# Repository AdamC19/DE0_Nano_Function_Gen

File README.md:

# DE0-Nano Function Gen
This repo contains the hardware files for a function generator built around the DE0-Nano FPGA dev board.

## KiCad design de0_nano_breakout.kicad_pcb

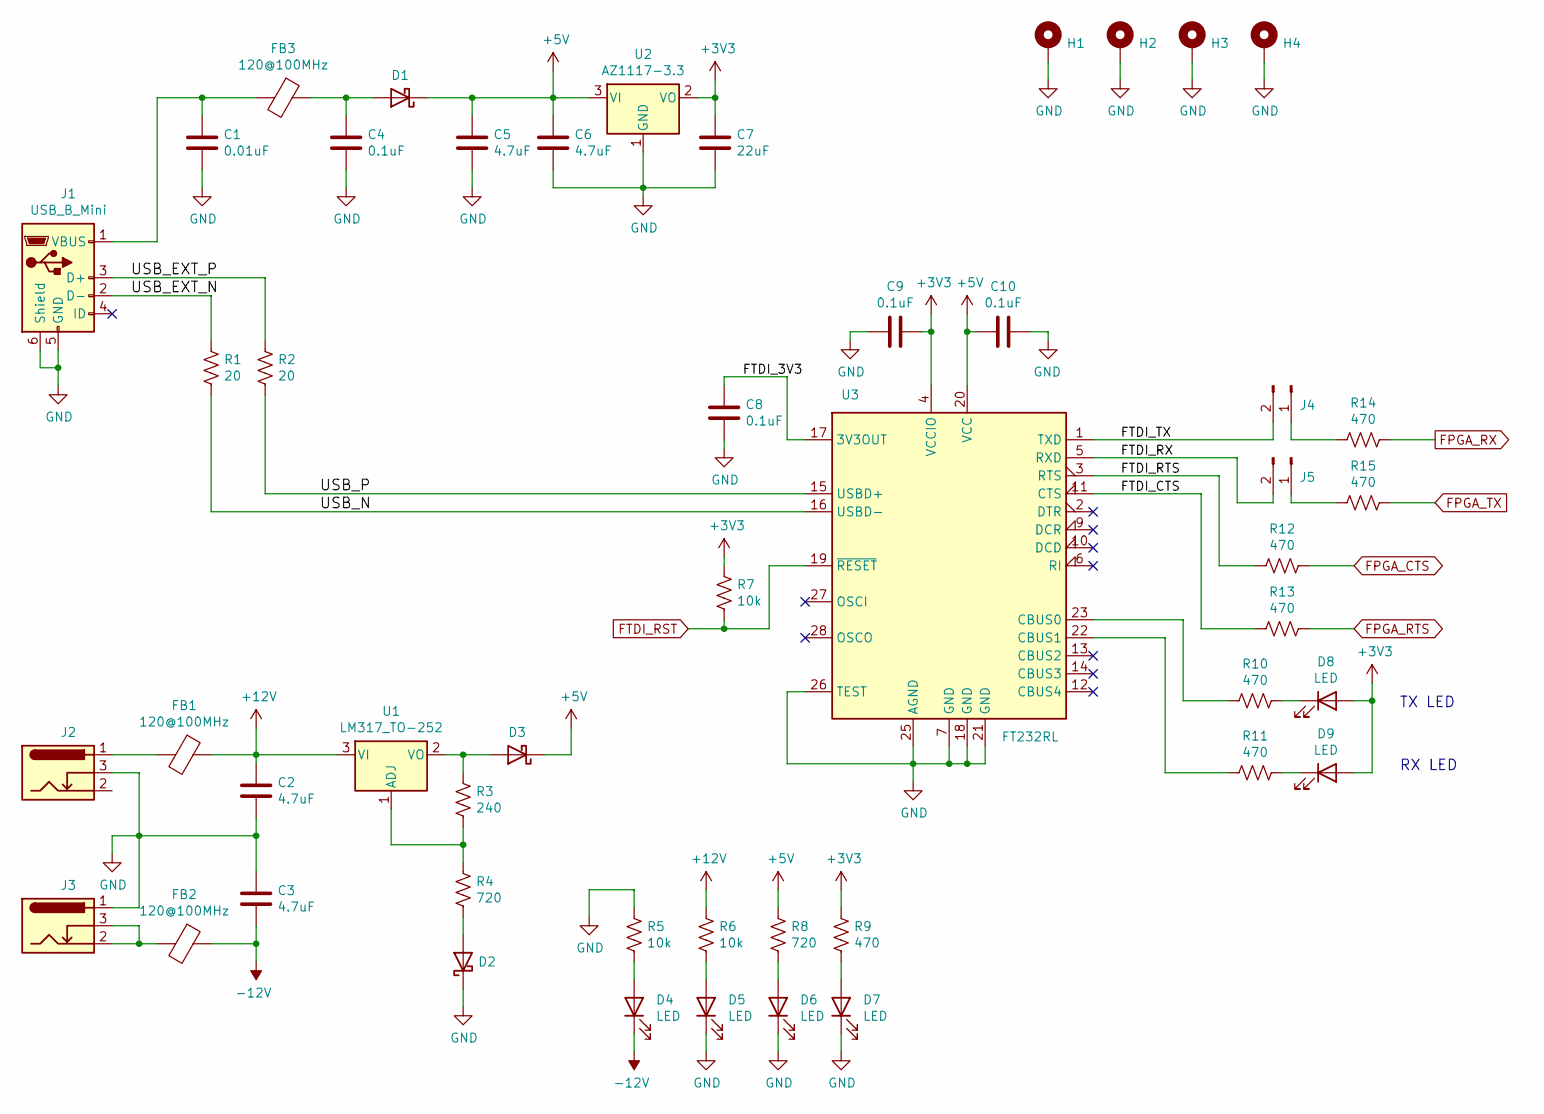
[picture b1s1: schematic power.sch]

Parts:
C1: 0.01uF; C_0603_1608Metric
C2, C3, C5, C6: 4.7uF; C_0805_2012Metric
C4, C8, C9, C10: 0.1uF; C_0603_1608Metric
C7: 22uF; C_1206_3216Metric
D1, D2, D3: D_Schottky; D_SMA
D4, D5, D6, D7, D8, D9: LED; LED_0603_1608Metric
FB1, FB2, FB3: 120@100MHz; L_0805_2012Metric
H1, H2, H3, H4: MountingHole_Pad; MountingHole_2.7mm_M2.5_Pad
J1: USB_B_Mini; USB_Mini-B_Wuerth_65100516121_Horizontal
J2, J3: Barrel_Jack_Switch; BarrelJack_Wuerth_6941xx301002
J4, J5: Conn_01x02_Male; PinHeader_1x02_P2.54mm_Vertical
R1, R2: 20; R_0805_2012Metric
R3: 240; R_0805_2012Metric
R4, R8: 720; R_0805_2012Metric
R5, R6, R7: 10k; R_0805_2012Metric
R9, R10, R11, R12, R13, R14, R15: 470; R_0805_2012Metric
U1: LM317_TO-252; TO-252-2
U2: AZ1117-3.3; SOT-89-3
U3: FT232RL; SSOP-28_5.3x10.2mm_P0.65mm

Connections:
+3V3: C7.1, C9.2, D8.2 (A), D9.2 (A), R7.1, R9.1, U2.2 (VO), U3.4 (VCCIO); also elsewhere on the board
+5V: C5.1, C6.1, C10.2, D1.1 (K), D3.1 (K), R8.1, U2.3 (VI), U3.20 (VCC); also elsewhere on the board
+12V: C2.1, FB1.1, R6.1, U1.3 (VI); also elsewhere on the board
-12V: C3.2, D4.1 (K), FB2.1; also elsewhere on the board
/Power/FTDI_3V3: C8.1, U3.17 (3V3OUT)
/Power/FTDI_CTS: R13.2, U3.11 (CTS)
/Power/FTDI_RTS: R12.2, U3.3 (RTS)
/Power/FTDI_RX: J5.2, U3.5 (RXD)
/Power/FTDI_TX: J4.2, U3.1 (TXD)
/Power/USB_EXT_N: J1.2 (D-), R1.2
/Power/USB_EXT_P: J1.3 (D+), R2.2
/Power/USB_N: R1.1, U3.16 (USBD-)
/Power/USB_P: R2.1, U3.15 (USBD+)
FPGA_CTS: R12.1; also elsewhere on the board
FPGA_RTS: R13.1; also elsewhere on the board
FPGA_RX: R14.1; also elsewhere on the board
FPGA_TX: R15.1; also elsewhere on the board
FTDI_RST: R7.2, U3.19 (~RESET~); also elsewhere on the board
GND: C1.2, C2.2, C3.1, C4.2, C5.2, C6.2, C7.2, C8.2, C9.1, C10.1, D2.1 (K), D5.1 (K), D6.1 (K), D7.1 (K), H1.1, H2.1, H3.1, H4.1, J1.5 (GND), J1.6 (Shield), J2.3, J3.1, R5.1, U2.1 (GND), U3.7 (GND), U3.18 (GND), U3.21 (GND), U3.25 (AGND), U3.26 (TEST); also elsewhere on the board
unnamed: C1.1, FB3.2, J1.1 (VBUS)
unnamed: C4.1, D1.2 (A), FB3.1
unnamed: D2.2 (A), R4.2
unnamed: D3.2 (A), R3.1, U1.2 (VO)
unnamed: D4.2 (A), R5.2
unnamed: D5.2 (A), R6.2
unnamed: D6.2 (A), R8.2
unnamed: D7.2 (A), R9.2
unnamed: D8.1 (K), R10.1
unnamed: D9.1 (K), R11.1
unnamed: FB1.2, J2.1
unnamed: FB2.2, J3.2, J3.3
unnamed: J4.1, R14.2
unnamed: J5.1, R15.2
unnamed: R3.2, R4.1, U1.1 (ADJ)
unnamed: R10.2, U3.23 (CBUS0)
unnamed: R11.2, U3.22 (CBUS1)

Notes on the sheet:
RX LED
TX LED

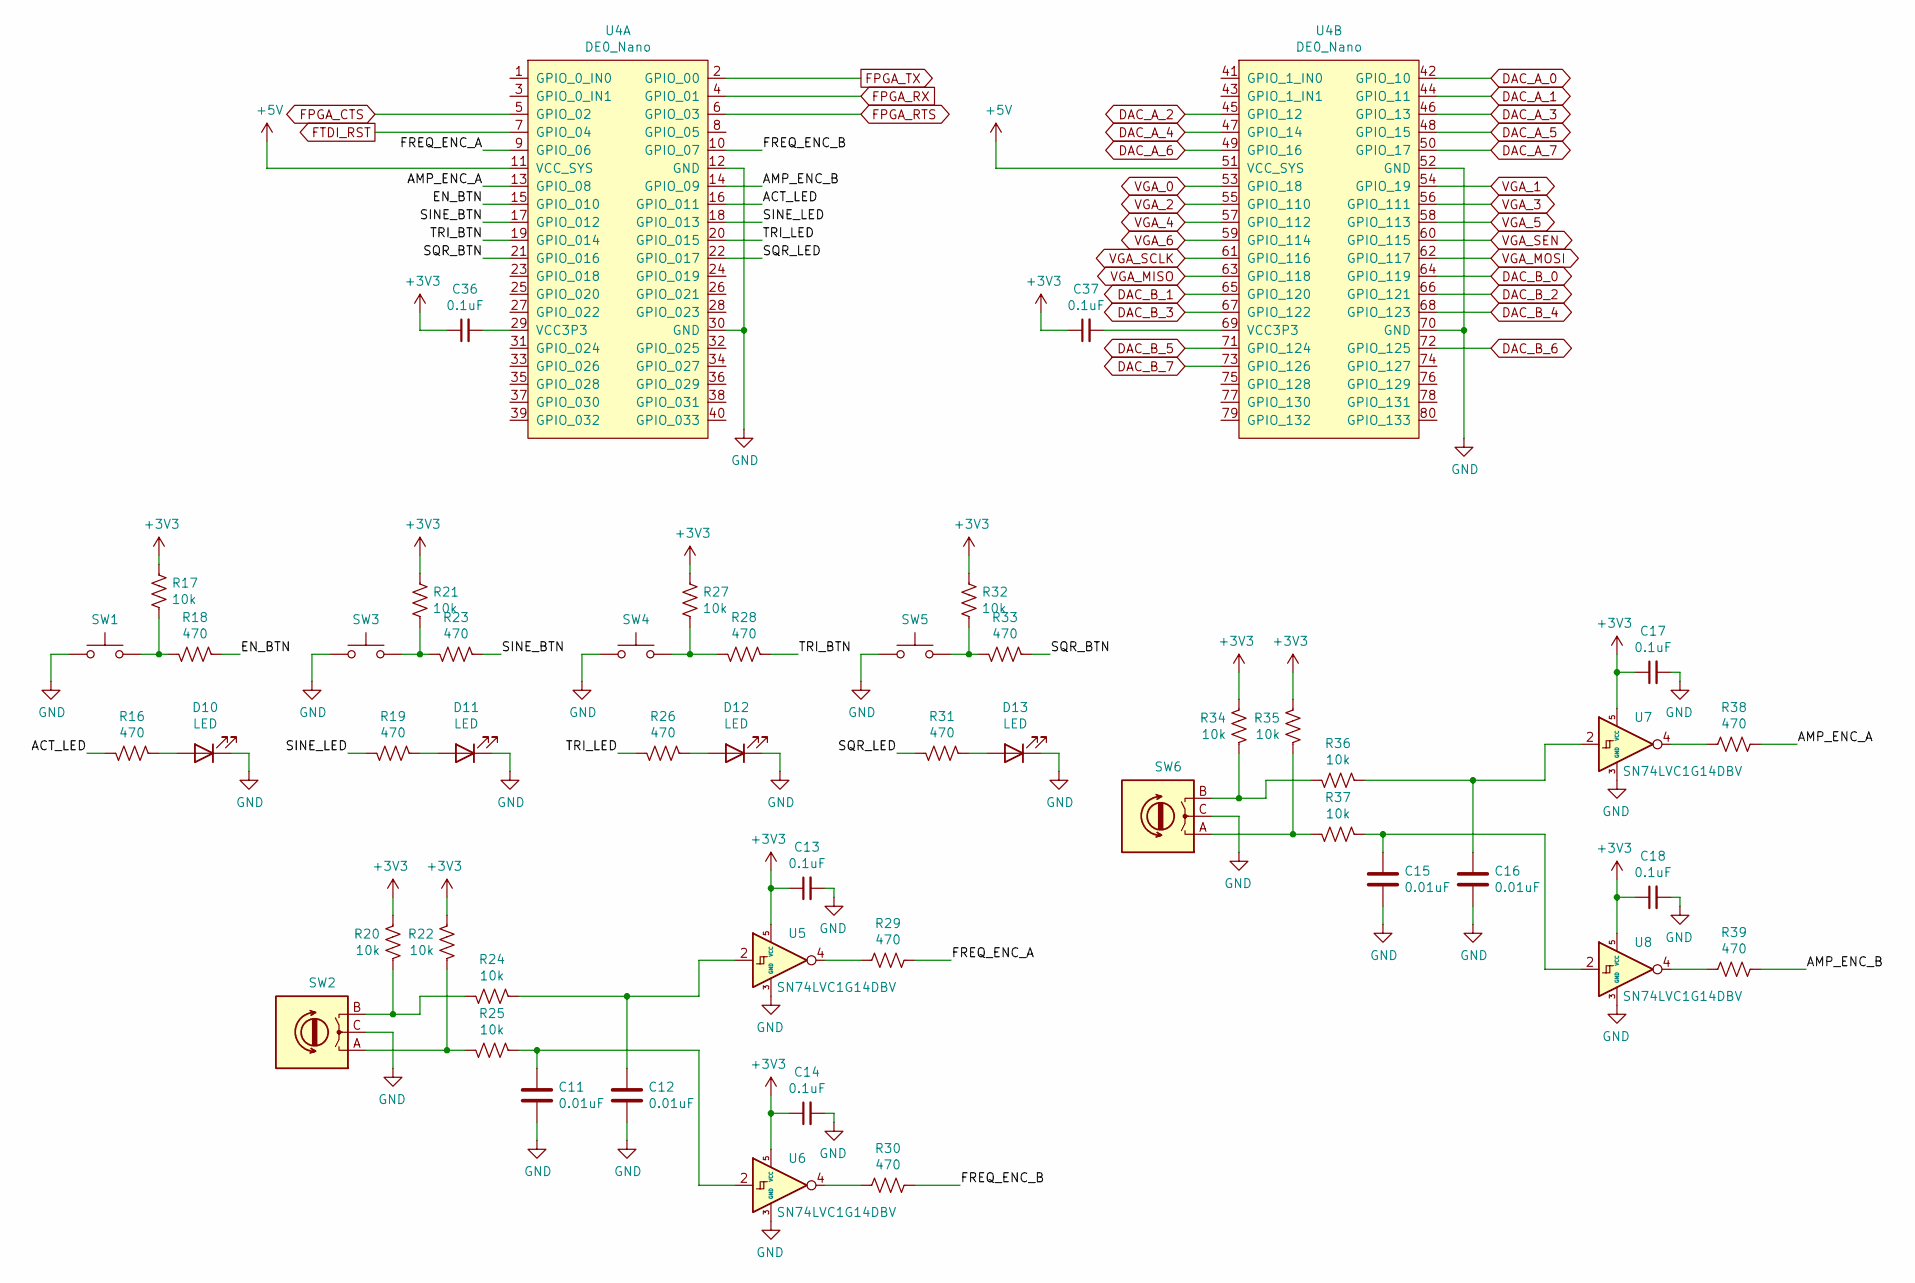
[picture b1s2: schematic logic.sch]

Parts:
C11, C12, C15, C16: 0.01uF; C_0603_1608Metric
C13, C14, C17, C18, C36, C37: 0.1uF; C_0603_1608Metric
D10, D11, D12, D13: LED; LED_0603_1608Metric
R16, R18, R19, R23, R26, R28, R29, R30, R31, R33, R38, R39: 470; R_0805_2012Metric
R17, R20, R21, R22, R24, R25, R27, R32, R34, R35, R36, R37: 10k; R_0805_2012Metric
SW1, SW3, SW4, SW5: SW_Push; SW_Push_1P1T_NO_CK_KSC6xxJ
SW2, SW6: Rotary_Encoder; RotaryEncoder_Alps_EC11E_Vertical_H20mm
U4: DE0_Nano
U5, U6, U7, U8: SN74LVC1G14DBV; SOT-23-5

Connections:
+3V3: C13.1, C14.1, C17.1, C18.1, C36.1, C37.1, R17.1, R20.1, R21.1, R22.1, R27.1, R32.1, R34.1, R35.1, U5.5 (VCC), U6.5 (VCC), U7.5 (VCC), U8.5 (VCC); also elsewhere on the board
+5V: U4.11 (VCC_SYS), U4.51 (VCC_SYS); also elsewhere on the board
/Logic/ACT_LED: R16.1, U4.16 (GPIO_011)
/Logic/AMP_ENC_A: R38.1, U4.13 (GPIO_08)
/Logic/AMP_ENC_B: R39.1, U4.14 (GPIO_09)
/Logic/EN_BTN: R18.2, U4.15 (GPIO_010)
/Logic/FREQ_ENC_A: R29.1, U4.9 (GPIO_06)
/Logic/FREQ_ENC_B: R30.1, U4.10 (GPIO_07)
/Logic/SINE_BTN: R23.2, U4.17 (GPIO_012)
/Logic/SINE_LED: R19.1, U4.18 (GPIO_013)
/Logic/SQR_BTN: R33.2, U4.21 (GPIO_016)
/Logic/SQR_LED: R31.1, U4.22 (GPIO_017)
/Logic/TRI_BTN: R28.2, U4.19 (GPIO_014)
/Logic/TRI_LED: R26.1, U4.20 (GPIO_015)
DAC_A_0: U4.42 (GPIO_10); also elsewhere on the board
DAC_A_1: U4.44 (GPIO_11); also elsewhere on the board
DAC_A_2: U4.45 (GPIO_12); also elsewhere on the board
DAC_A_3: U4.46 (GPIO_13); also elsewhere on the board
DAC_A_4: U4.47 (GPIO_14); also elsewhere on the board
DAC_A_5: U4.48 (GPIO_15); also elsewhere on the board
DAC_A_6: U4.49 (GPIO_16); also elsewhere on the board
DAC_A_7: U4.50 (GPIO_17); also elsewhere on the board
DAC_B_0: U4.64 (GPIO_119); also elsewhere on the board
DAC_B_1: U4.65 (GPIO_120); also elsewhere on the board
DAC_B_2: U4.66 (GPIO_121); also elsewhere on the board
DAC_B_3: U4.67 (GPIO_122); also elsewhere on the board
DAC_B_4: U4.68 (GPIO_123); also elsewhere on the board
DAC_B_5: U4.71 (GPIO_124); also elsewhere on the board
DAC_B_6: U4.72 (GPIO_125); also elsewhere on the board
DAC_B_7: U4.73 (GPIO_126); also elsewhere on the board
FPGA_CTS: U4.5 (GPIO_02); also elsewhere on the board
FPGA_RTS: U4.6 (GPIO_03); also elsewhere on the board
FPGA_RX: U4.4 (GPIO_01); also elsewhere on the board
FPGA_TX: U4.2 (GPIO_00); also elsewhere on the board
FTDI_RST: U4.7 (GPIO_04); also elsewhere on the board
GND: C11.2, C12.2, C13.2, C14.2, C15.2, C16.2, C17.2, C18.2, D10.1 (K), D11.1 (K), D12.1 (K), D13.1 (K), SW1.1, SW2.C, SW3.1, SW4.1, SW5.1, SW6.C, U4.12 (GND), U4.30 (GND), U4.52 (GND), U4.70 (GND), U5.3 (GND), U6.3 (GND), U7.3 (GND), U8.3 (GND); also elsewhere on the board
unnamed: C11.1, R25.2, U6.2
unnamed: C12.1, R24.2, U5.2
unnamed: C15.1, R37.2, U8.2
unnamed: C16.1, R36.2, U7.2
unnamed: C36.2, U4.29 (VCC3P3)
unnamed: C37.2, U4.69 (VCC3P3)
unnamed: D10.2 (A), R16.2
unnamed: D11.2 (A), R19.2
unnamed: D12.2 (A), R26.2
unnamed: D13.2 (A), R31.2
unnamed: R17.2, R18.1, SW1.2
unnamed: R20.2, R24.1, SW2.B
unnamed: R21.2, R23.1, SW3.2
unnamed: R22.2, R25.1, SW2.A
unnamed: R27.2, R28.1, SW4.2
unnamed: R29.2, U5.4
unnamed: R30.2, U6.4
unnamed: R32.2, R33.1, SW5.2
unnamed: R34.2, R36.1, SW6.B
unnamed: R35.2, R37.1, SW6.A
unnamed: R38.2, U7.4
unnamed: R39.2, U8.4
VGA_0: U4.53 (GPIO_18); also elsewhere on the board
VGA_1: U4.54 (GPIO_19); also elsewhere on the board
VGA_2: U4.55 (GPIO_110); also elsewhere on the board
VGA_3: U4.56 (GPIO_111); also elsewhere on the board
VGA_4: U4.57 (GPIO_112); also elsewhere on the board
VGA_5: U4.58 (GPIO_113); also elsewhere on the board
VGA_6: U4.59 (GPIO_114); also elsewhere on the board
VGA_MISO: U4.63 (GPIO_118); also elsewhere on the board
VGA_MOSI: U4.62 (GPIO_117); also elsewhere on the board
VGA_SCLK: U4.61 (GPIO_116); also elsewhere on the board
VGA_SEN: U4.60 (GPIO_115); also elsewhere on the board

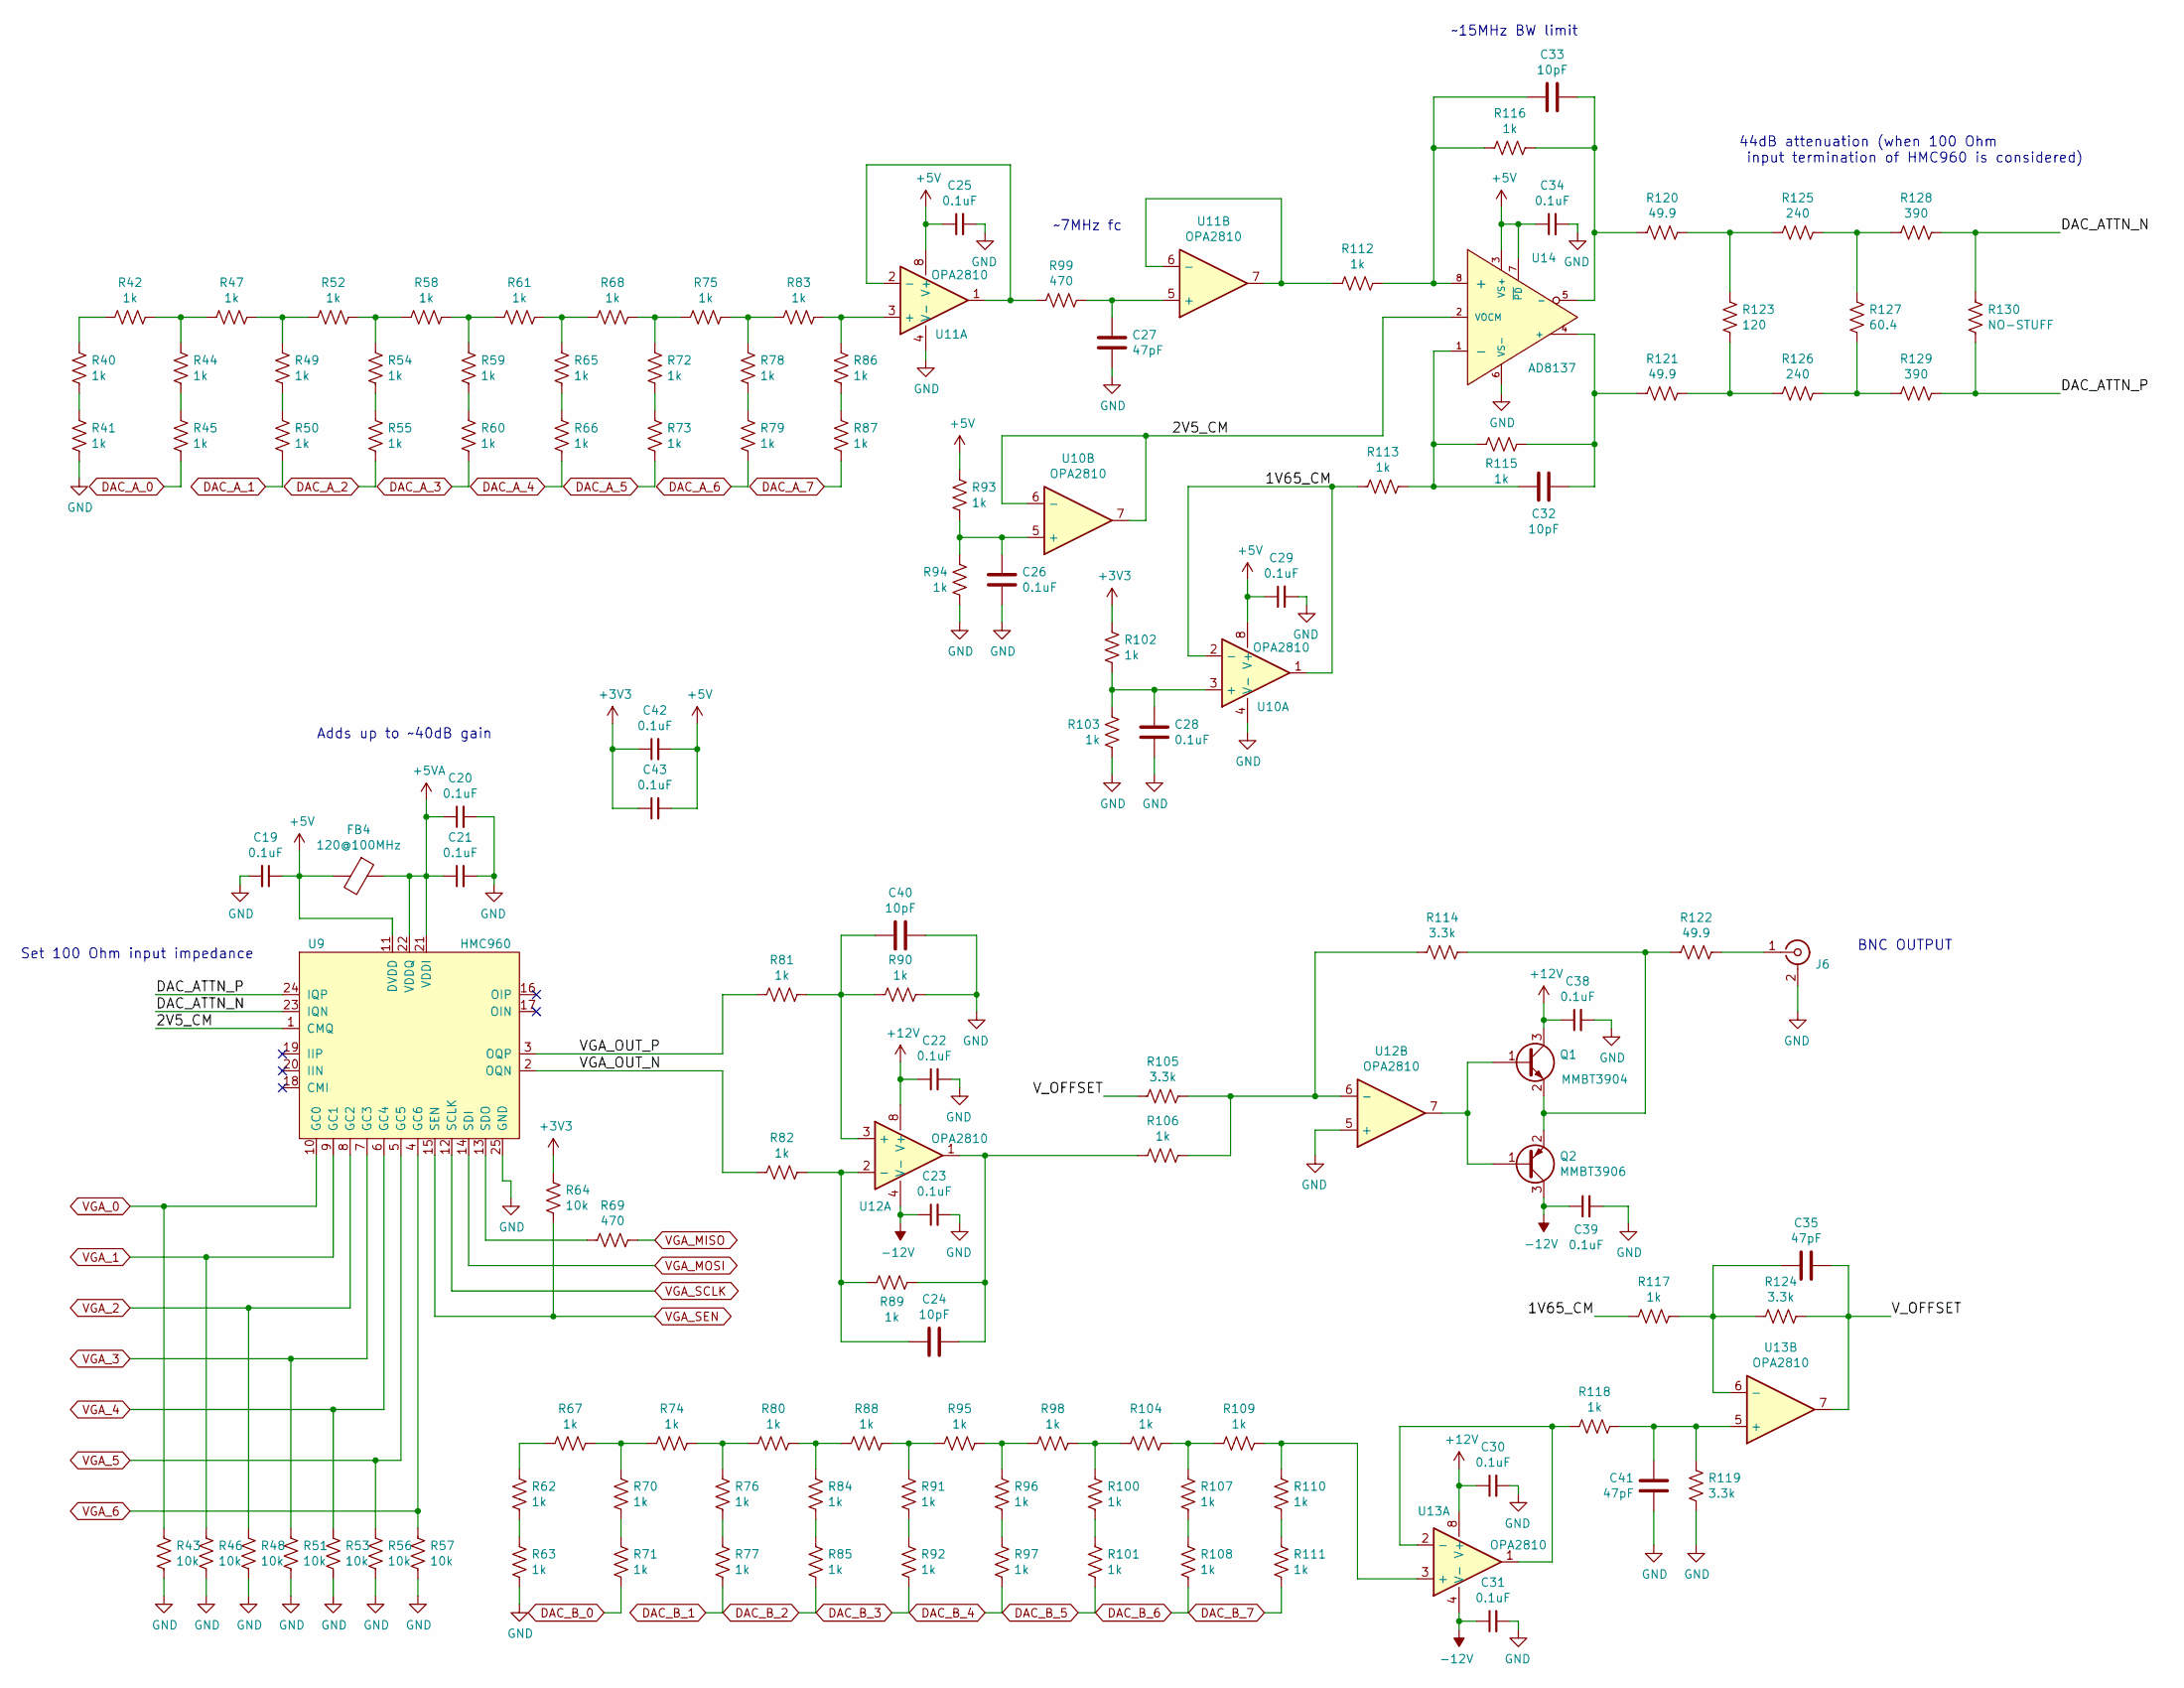
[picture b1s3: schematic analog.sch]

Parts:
C19, C20, C21, C22, C23, C25, C26, C28, C29, C30, C31, C34, C38, C39, C42, C43: 0.1uF; C_0603_1608Metric
C24, C32, C33, C40: 10pF; C_0603_1608Metric
C27, C35, C41: 47pF; C_0603_1608Metric
FB4: 120@100MHz; L_0805_2012Metric
J6: 031-5329-51RFX; Amphenol_31-5329-51RFX; MFG_PN 031-5329-51RFX
Q1: MMBT3904; SOT-23
Q2: MMBT3906; SOT-23
R40, R41, R42, R44, R45, R47, R49, R50, R52, R54, R55, R58, R59, R60, R61, R62, R63, R65, R66, R67, R68, R70, R71, R72, R73, R74, R75, R76, R77, R78, R79, R80, R81, R82, R83, R84, R85, R86, R87, R88, R89, R90, R91, R92, R93, R94, R95, R96, R97, R98, R100, R101, R102, R103, R104, R106, R107, R108, R109, R110, R111, R112, R113, R115, R116, R117, R118: 1k; R_0805_2012Metric
R43, R46, R48, R51, R53, R56, R57, R64: 10k; R_0805_2012Metric
R69, R99: 470; R_0805_2012Metric
R105, R114, R119, R124: 3.3k; R_0805_2012Metric
R120, R121, R122: 49.9; R_1206_3216Metric
R123: 120; R_0805_2012Metric
R125, R126: 240; R_0805_2012Metric
R127: 60.4; R_0805_2012Metric
R128, R129: 390; R_0805_2012Metric
R130: NO-STUFF; R_0805_2012Metric
U9: HMC960; QFN-24-1EP_4x4mm_P0.5mm_EP2.7x2.7mm
U10, U11, U12, U13: OPA2810; SOIC-8_3.9x4.9mm_P1.27mm
U14: AD8137; SOIC-8_3.9x4.9mm_P1.27mm

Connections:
+3V3: C42.1, C43.1, R64.2, R102.1; also elsewhere on the board
+5V: C19.1, C25.1, C29.1, C34.1, C42.2, C43.2, FB4.2, R93.1, U9.11 (DVDD), U10.8 (V+), U11.8 (V+), U14.3 (VS+), U14.7 (~PD); also elsewhere on the board
+5VA: C20.1, C21.1, FB4.1, U9.21 (VDDI), U9.22 (VDDQ)
+12V: C22.1, C30.1, C38.1, Q1.3 (C), U12.8 (V+), U13.8 (V+); also elsewhere on the board
-12V: C23.1, C31.1, C39.1, Q2.3 (C), U12.4 (V-), U13.4 (V-); also elsewhere on the board
/Analog/1V65_CM: R113.2, R117.1, U10.1, U10.2 (-)
/Analog/2V5_CM: U9.1 (CMQ), U10.6 (-), U10.7, U14.2 (VOCM)
/Analog/DAC_ATTN_N: R128.1, R130.1, U9.23 (IQN)
/Analog/DAC_ATTN_P: R129.1, R130.2, U9.24 (IQP)
/Analog/VGA_OUT_N: R82.1, U9.2 (OQN)
/Analog/VGA_OUT_P: R81.2, U9.3 (OQP)
/Analog/V_OFFSET: C35.2, R105.2, R124.1, U13.7
DAC_A_0: R45.2; also elsewhere on the board
DAC_A_1: R50.2; also elsewhere on the board
DAC_A_2: R55.2; also elsewhere on the board
DAC_A_3: R60.2; also elsewhere on the board
DAC_A_4: R66.2; also elsewhere on the board
DAC_A_5: R73.2; also elsewhere on the board
DAC_A_6: R79.2; also elsewhere on the board
DAC_A_7: R87.2; also elsewhere on the board
DAC_B_0: R71.2; also elsewhere on the board
DAC_B_1: R77.2; also elsewhere on the board
DAC_B_2: R85.2; also elsewhere on the board
DAC_B_3: R92.2; also elsewhere on the board
DAC_B_4: R97.2; also elsewhere on the board
DAC_B_5: R101.2; also elsewhere on the board
DAC_B_6: R108.2; also elsewhere on the board
DAC_B_7: R111.2; also elsewhere on the board
GND: C19.2, C20.2, C21.2, C22.2, C23.2, C25.2, C26.2, C27.2, C28.2, C29.2, C30.2, C31.2, C34.2, C38.2, C39.2, C40.2, C41.1, J6.2 (Ext), R41.2, R43.1, R46.1, R48.1, R51.1, R53.1, R56.1, R57.1, R63.2, R90.1, R94.2, R103.2, R119.1, U9.25 (GND), U10.4 (V-), U11.4 (V-), U12.5 (+), U14.6 (VS-); also elsewhere on the board
unnamed: C24.1, R82.2, R89.1, U12.2 (-)
unnamed: C24.2, R89.2, R106.2, U12.1
unnamed: C26.1, R93.2, R94.1, U10.5 (+)
unnamed: C27.1, R99.1, U11.5 (+)
unnamed: C28.1, R102.2, R103.1, U10.3 (+)
unnamed: C32.1, R113.1, R115.1, U14.1 (-)
unnamed: C32.2, R115.2, R121.1, U14.4 (+)
unnamed: C33.1, R112.2, R116.1, U14.8 (+)
unnamed: C33.2, R116.2, R120.1, U14.5 (-)
unnamed: C35.1, R117.2, R124.2, U13.6 (-)
unnamed: C40.1, R81.1, R90.2, U12.3 (+)
unnamed: C41.2, R118.2, R119.2, U13.5 (+)
unnamed: J6.1 (In), R122.2
unnamed: Q1.1 (B), Q2.1 (B), U12.7
unnamed: Q1.2 (E), Q2.2 (E), R114.1, R122.1
unnamed: R40.1, R42.1
unnamed: R40.2, R41.1
unnamed: R42.2, R44.1, R47.1
unnamed: R44.2, R45.1
unnamed: R47.2, R49.1, R52.1
unnamed: R49.2, R50.1
unnamed: R52.2, R54.1, R58.1
unnamed: R54.2, R55.1
unnamed: R58.2, R59.1, R61.1
unnamed: R59.2, R60.1
unnamed: R61.2, R65.1, R68.1
unnamed: R62.1, R67.1
unnamed: R62.2, R63.1
unnamed: R65.2, R66.1
unnamed: R67.2, R70.1, R74.1
unnamed: R68.2, R72.1, R75.1
unnamed: R69.2, U9.13 (SDO)
unnamed: R70.2, R71.1
unnamed: R72.2, R73.1
unnamed: R74.2, R76.1, R80.1
unnamed: R75.2, R78.1, R83.1
unnamed: R76.2, R77.1
unnamed: R78.2, R79.1
unnamed: R80.2, R84.1, R88.1
unnamed: R83.2, R86.1, U11.3 (+)
unnamed: R84.2, R85.1
unnamed: R86.2, R87.1
unnamed: R88.2, R91.1, R95.1
unnamed: R91.2, R92.1
unnamed: R95.2, R96.1, R98.1
unnamed: R96.2, R97.1
unnamed: R99.2, U11.1, U11.2 (-)
unnamed: R98.2, R100.1, R104.1
unnamed: R100.2, R101.1
unnamed: R104.2, R107.1, R109.1
unnamed: R105.1, R106.1, R114.2, U12.6 (-)
unnamed: R107.2, R108.1
unnamed: R109.2, R110.1, U13.3 (+)
unnamed: R110.2, R111.1
unnamed: R112.1, U11.6 (-), U11.7
unnamed: R118.1, U13.1, U13.2 (-)
unnamed: R120.2, R123.2, R125.2
unnamed: R121.2, R123.1, R126.2
unnamed: R125.1, R127.2, R128.2
unnamed: R126.1, R127.1, R129.2
VGA_0: R43.2, U9.10 (GC0); also elsewhere on the board
VGA_1: R46.2, U9.9 (GC1); also elsewhere on the board
VGA_2: R48.2, U9.8 (GC2); also elsewhere on the board
VGA_3: R51.2, U9.7 (GC3); also elsewhere on the board
VGA_4: R53.2, U9.6 (GC4); also elsewhere on the board
VGA_5: R56.2, U9.5 (GC5); also elsewhere on the board
VGA_6: R57.2, U9.4 (GC6); also elsewhere on the board
VGA_MISO: R69.1; also elsewhere on the board
VGA_MOSI: U9.14 (SDI); also elsewhere on the board
VGA_SCLK: U9.12 (SCLK); also elsewhere on the board
VGA_SEN: R64.1, U9.15 (SEN); also elsewhere on the board

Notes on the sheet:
~~7MHz fc
~~15MHz BW limit
44dB attenuation (when 100 Ohm input termination of HMC960 is considered)
Adds up to ~~40dB gain
BNC OUTPUT
Set 100 Ohm input impedance

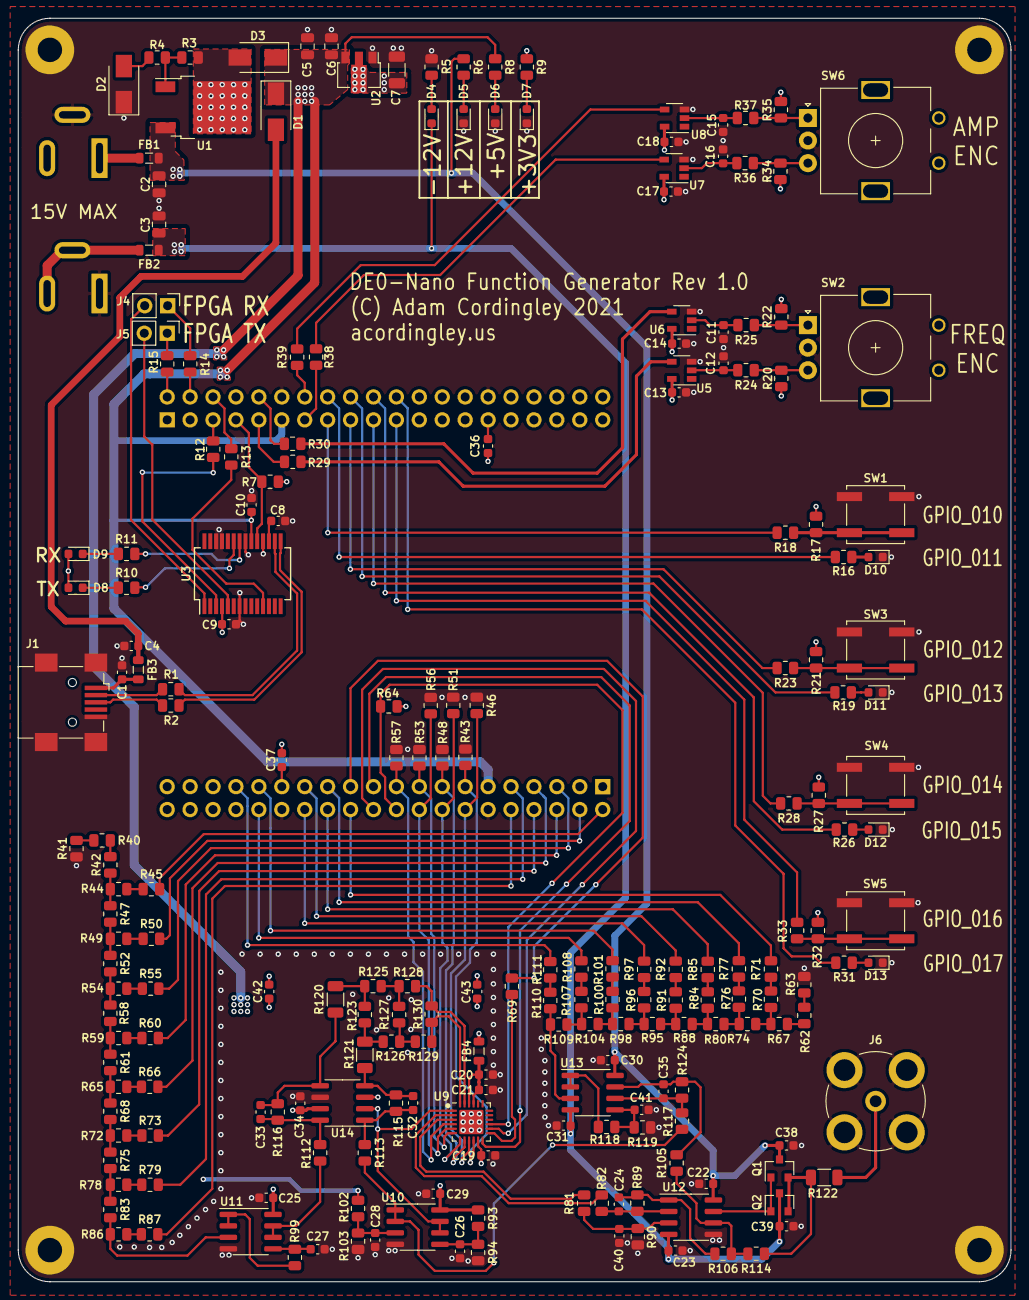
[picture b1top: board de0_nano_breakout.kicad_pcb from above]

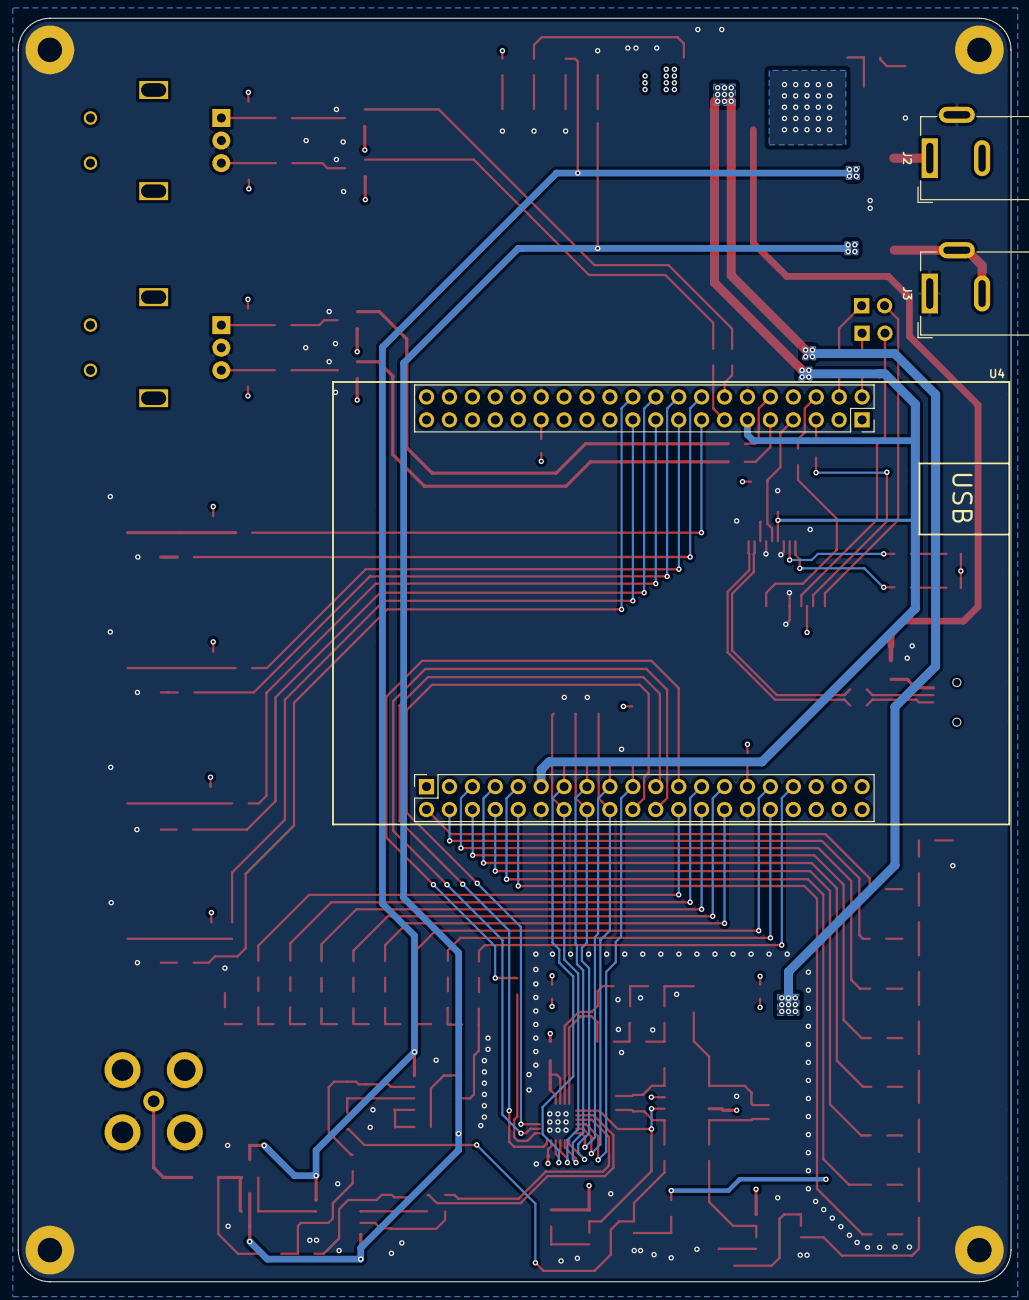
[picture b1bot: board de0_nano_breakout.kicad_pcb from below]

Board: 4 copper layers, 110.0 x 140.0 mm, 222 parts (3 on the bottom side), 165 nets.
